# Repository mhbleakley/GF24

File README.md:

# GeoFence 2024

A dog collar with GNSS capabilities and an alarm, allowing the user to set a virtual fenced area. When the collar leaves the fenced area, the alarm sounds.

View schematic/board [here](https://kicanvas.org/?github=https%3A%2F%2Fgithub.com%2Fmhbleakley%2FGF24) (you will have to select board or schematic from right panel).

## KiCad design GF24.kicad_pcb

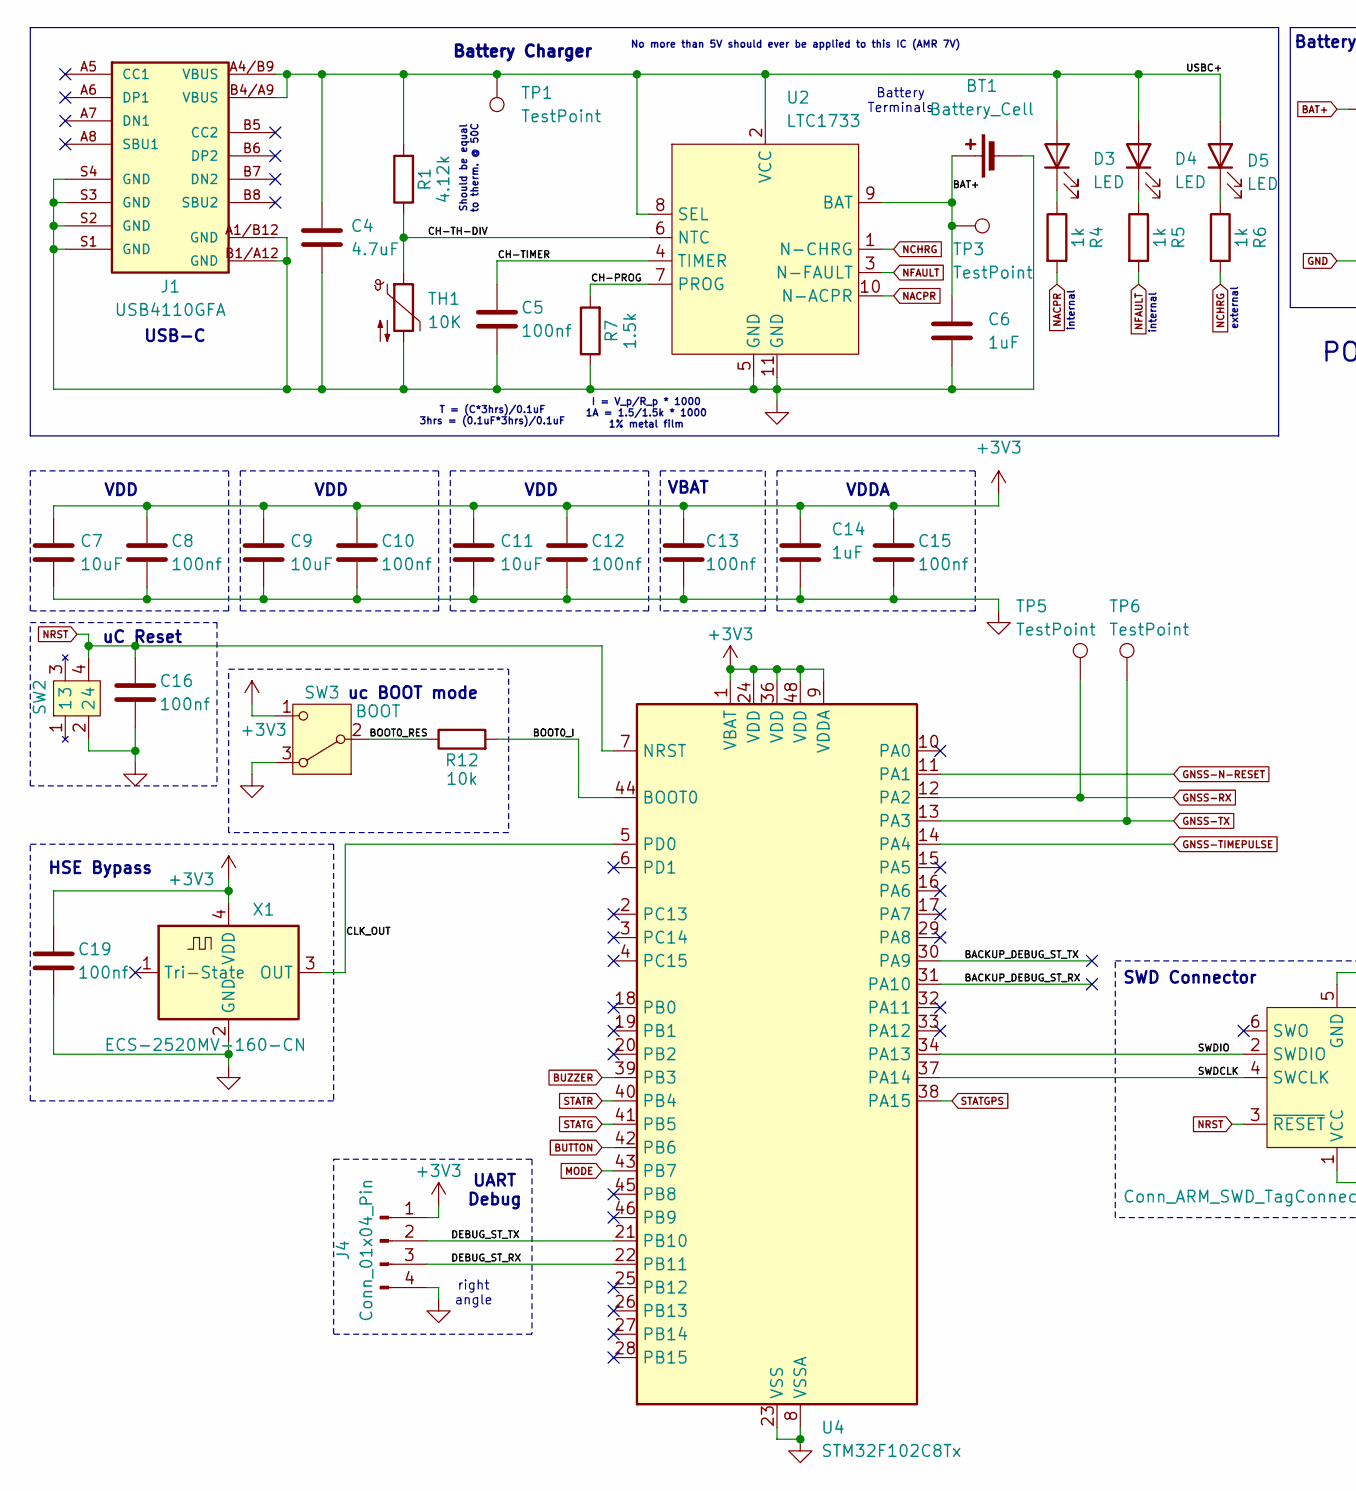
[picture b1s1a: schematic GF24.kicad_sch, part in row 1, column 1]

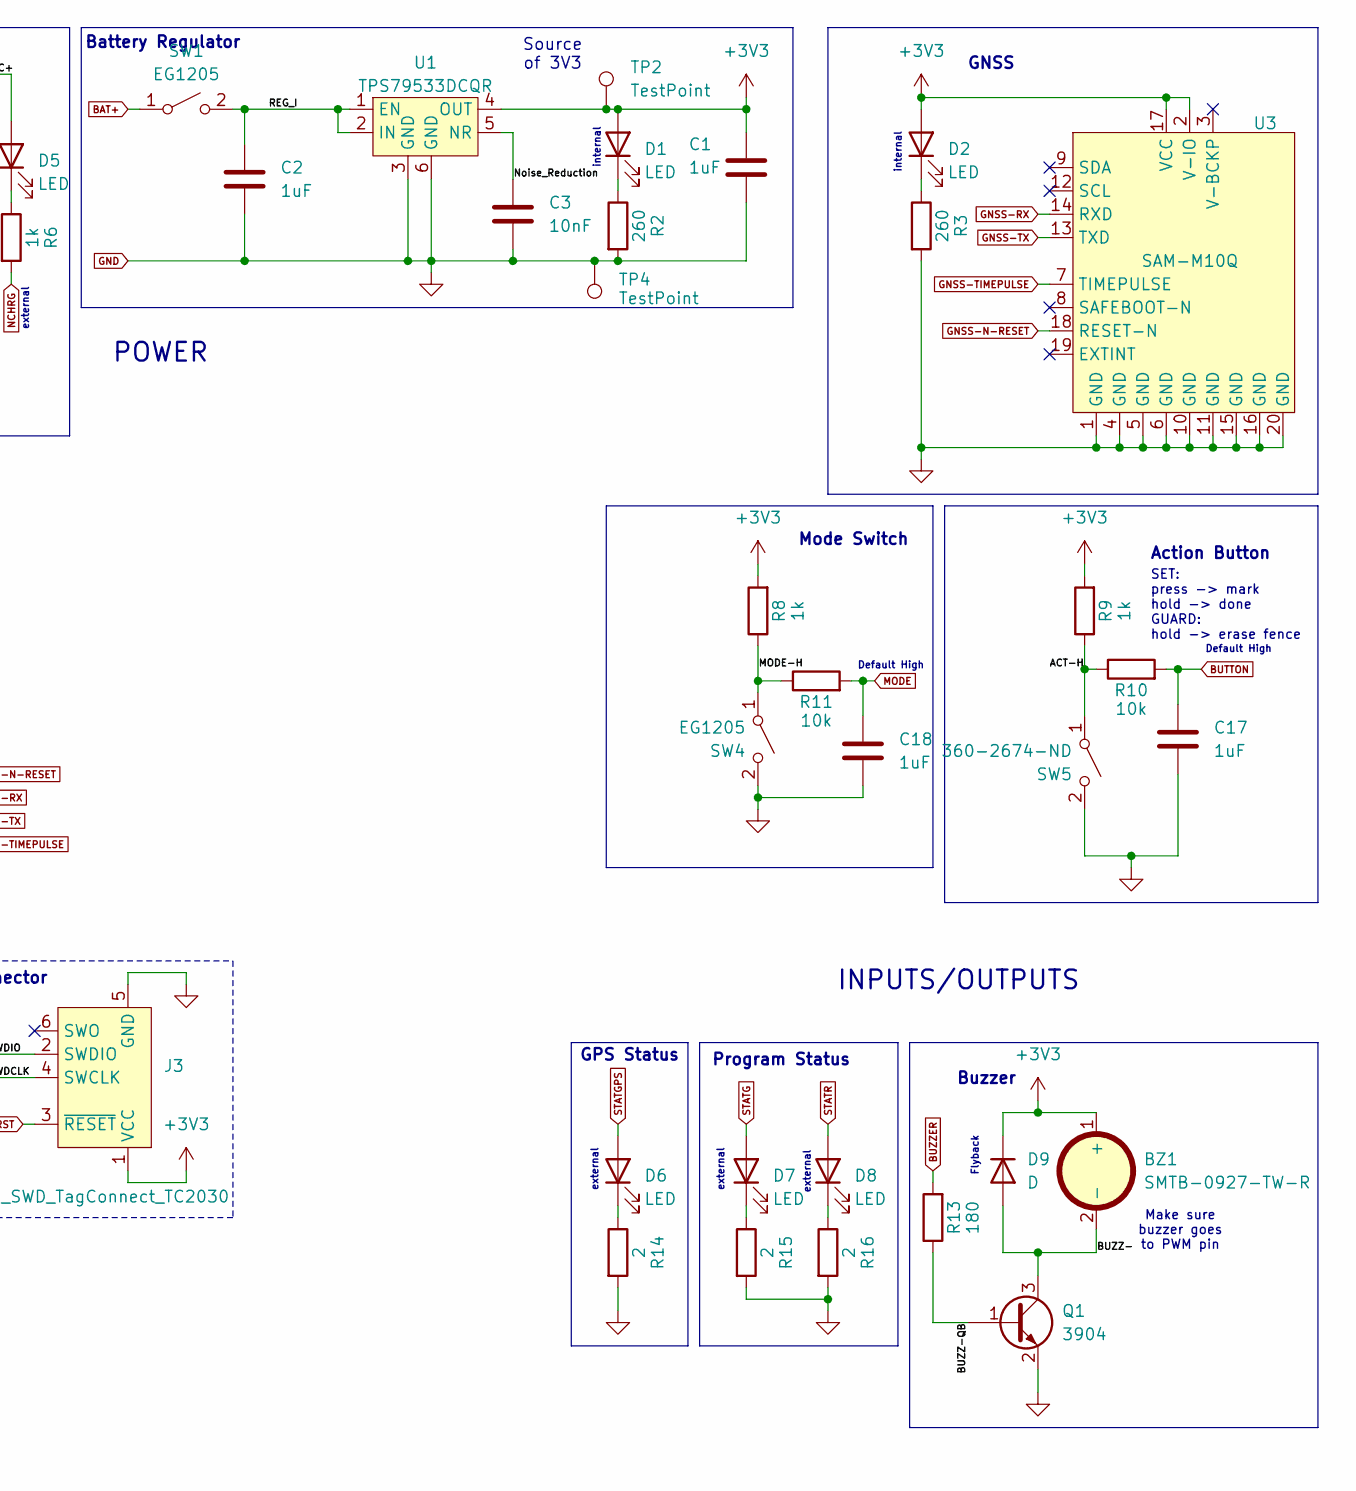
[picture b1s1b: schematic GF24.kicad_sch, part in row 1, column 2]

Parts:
BT1: Battery_Cell; Solder_Joint_1_2
BZ1: SMTB-0927-TW-R; Manufacturer PN 668-SMTB-0927-TW-RTR-ND
C1, C2, C6, C14, C17, C18: 1uF; C_0603_1608Metric; Manufacturer PN 399-13217-2-ND
C3: 10nF; C_0603_1608Metric; Manufacturer PN 399-C0603C103K8RACTUTR-ND
C4: 4.7uF; C_0805_2012Metric; Manufacturer PN 399-C1210C475K8RACTUTR-ND
C5, C8, C10, C12, C13, C15, C16, C19: 100nf; C_0805_2012Metric; Manufacturer PN 399-C0805C104K8RACTUTR-ND
C7, C9, C11: 10uF; C_0805_2012Metric; Manufacturer PN 399-C1210C106K8RACTUTR-ND
D1, D2, D3, D4: LED; WE-0603-Mono-Chip-Advance; Manufacturer PN 732-150060RS75003TR-ND
D5, D6, D7, D8: LED; WE-1204-Mono-Side; Manufacturer PN 732-5024-2-ND
D9: D; SOD-123-2; Manufacturer PN MMSD4148T1GOSTR-ND
J1: USB4110GFA; GCT_USB4110GFA; Manufacturer PN 2073-USB4110-GF-A-2-ND; DigiKey_Part_Number 2073-USB4110-GF-A-2-ND
J3: Conn_ARM_SWD_TagConnect_TC2030; Tag-Connect_TC2030-IDC-FP_2x03_P1.27mm_Vertical
J4: Conn_01x04_Pin; PinHeader_1x04_P2.54mm_Horizontal; Manufacturer PN S9016E-04-ND
Q1: 3904; SOT-323_SC-70; Manufacturer PN MMBT3904LT1GOSTR-ND
R1: 4.12k; R0603_medium; Manufacturer PN 311-4.12KHRTR-ND
R2, R3: 260; R0603_medium; Manufacturer PN 311-261HRTR-ND
R4, R5, R6, R8, R9: 1k; R0603_medium; Manufacturer PN 311-1.00KHRTR-ND
R7: 1.5k; R0603_medium; Manufacturer PN 311-1.50KHRTR-ND
R10, R11, R12: 10k; R0603_medium; Manufacturer PN 311-10.0KHRTR-ND
R13: 180; R0603_medium; Manufacturer PN 311-180HRTR-ND
R14, R15, R16: 2; R0603_medium; Manufacturer PN 13-RC0603JR-072RLTR-ND
SW1, SW4: EG1205; Solder_Joint_1_2
SW2: PTS815SJM250SMTRLFS; Manufacturer PN CKN12215-2-ND
SW3: BOOT; Nidec_Copal_CAS-120A; Manufacturer PN 563-1021-2-ND
SW5: 360-2674-ND; Solder_Joint_1_2
TH1: 10K; R0603_medium; Manufacturer PN 490-18139-2-ND
TP1, TP2, TP3, TP4, TP5, TP6: TestPoint; TestPoint_Pad_D1.5mm
U1: TPS79533DCQR; SOT-223-6; Manufacturer PN 296-13810-2-ND
U2: LTC1733; 10-MSOP-TE; Manufacturer PN LTC1733EMSE#TRPBFTR-ND
U3: SAM-M10Q; Manufacturer PN 672-SAM-M10Q-00BTR-ND
U4: STM32F102C8Tx; LQFP-48_7x7mm_P0.5mm; Manufacturer PN 497-8307-ND
X1: ECS-2520MV-160-CN; Oscillator_SMD_ECS_2520MV-xxx-xx-4Pin_2.5x2.0mm; Manufacturer PN XC3030TR-ND

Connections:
+3V3: BZ1.1 (+), C1.1, C7.1, C8.1, C9.1, C10.1, C11.1, C12.1, C13.1, C14.1, C15.1, C19.1, D1.2 (A), D2.2 (A), D9.1 (K), J3.1 (VCC), J4.1, R8.2, R9.2, SW3.1 (C), TP2.1, U1.4 (OUT), U3.2 (V-IO), U3.17 (VCC), U4.1 (VBAT), U4.9 (VDDA), U4.24 (VDD), U4.36 (VDD), U4.48 (VDD), X1.4 (VDD)
/ACT-H: R9.1, R10.1, SW5.1 (A)
/BACKUP_DEBUG_ST_RX: U4.31 (PA10)
/BACKUP_DEBUG_ST_TX: U4.30 (PA9)
/BOOT0_I: R12.2, U4.44 (BOOT0)
/BOOT0_RES: R12.1, SW3.2 (B)
/BUZZ-: BZ1.2 (-), D9.2 (A), Q1.3 (C)
/BUZZ-QB: Q1.1 (B), R13.1
/CH-PROG: R7.2, U2.7 (PROG)
/CH-TH-DIV: R1.1, TH1.1, U2.6 (NTC)
/CH-TIMER: C5.1, U2.4 (TIMER)
/CLK_OUT: U4.5 (PD0), X1.3 (OUT)
/DEBUG_ST_RX: J4.3, U4.22 (PB11)
/DEBUG_ST_TX: J4.2, U4.21 (PB10)
/MODE-H: R8.1, R11.1, SW4.1 (A)
/Noise_Reduction: C3.1, U1.5 (NR)
/REG_I: C2.1, SW1.2 (B), U1.1 (EN), U1.2 (IN)
/SWDCLK: J3.4 (SWCLK), U4.37 (PA14)
/SWDIO: J3.2 (SWDIO), U4.34 (PA13)
/USBC+: C4.1, D3.2 (A), D4.2 (A), D5.2 (A), J1.A4/B9 (VBUS), J1.B4/A9 (VBUS), R1.2, TP1.1, U2.2 (VCC), U2.8 (SEL)
BAT+: BT1.1 (+), C6.1, SW1.1 (A), TP3.1, U2.9 (BAT)
BUTTON: C17.1, R10.2, U4.42 (PB6)
BUZZER: R13.2, U4.39 (PB3)
GND: BT1.2 (-), C1.2, C2.2, C3.2, C4.2, C5.2, C6.2, C7.2, C8.2, C9.2, C10.2, C11.2, C12.2, C13.2, C14.2, C15.2, C16.2, C17.2, C18.2, C19.2, J1.A1/B12 (GND), J1.B1/A12 (GND), J1.S1 (GND), J1.S2 (GND), J1.S3 (GND), J1.S4 (GND), J3.5 (GND), J4.4, Q1.2 (E), R2.2, R3.2, R7.1, R14.2, R15.2, R16.2, SW2.2, SW3.3 (A), SW4.2 (B), SW5.2 (B), TH1.2, TP4.1, U1.3 (GND), U1.6 (GND), U2.5 (GND), U2.11 (GND), U3.1 (GND), U3.4 (GND), U3.5 (GND), U3.6 (GND), U3.10 (GND), U3.11 (GND), U3.15 (GND), U3.16 (GND), U3.20 (GND), U4.8 (VSSA), U4.23 (VSS), U4.35 (VSS), U4.47 (VSS), X1.2 (GND)
GNSS-N-RESET: U3.18 (RESET-N), U4.11 (PA1)
GNSS-RX: TP5.1, U3.14 (RXD), U4.12 (PA2)
GNSS-TIMEPULSE: U3.7 (TIMEPULSE), U4.14 (PA4)
GNSS-TX: TP6.1, U3.13 (TXD), U4.13 (PA3)
MODE: C18.1, R11.2, U4.43 (PB7)
NACPR: R4.2, U2.10 (N-ACPR)
NCHRG: R6.2, U2.1 (N-CHRG)
NFAULT: R5.2, U2.3 (N-FAULT)
NRST: C16.1, J3.3 (~RESET), SW2.4, U4.7 (NRST)
unnamed: D1.1 (K), R2.1
unnamed: D2.1 (K), R3.1
unnamed: D3.1 (K), R4.1
unnamed: D4.1 (K), R5.1
unnamed: D5.1 (K), R6.1
unnamed: D6.1 (K), R14.1
unnamed: D7.1 (K), R15.1
unnamed: D8.1 (K), R16.1
STATG: D7.2 (A), U4.41 (PB5)
STATGPS: D6.2 (A), U4.38 (PA15)
STATR: D8.2 (A), U4.40 (PB4)

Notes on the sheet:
Default High
SET: press -> mark hold -> done GUARD: hold -> erase fence
VDD
Should be equal to therm. @ 50C
external
Battery Terminals
INPUTS/OUTPUTS
internal
VDDA
USB-C
Buzzer
POWER
GNSS
right angle
uc BOOT mode
Mode Switch
Flyback
T = (C*3hrs)/0.1uF 3hrs = (0.1uF*3hrs)/0.1uF
UART Debug
uC Reset
Program Status
SWD Connector
GPS Status
No more than 5V should ever be applied to this IC (AMR 7V)
Source of 3V3
VBAT
Make sure buzzer goes to PWM pin
Battery Regulator
HSE Bypass
I = V_p/R_p * 1000 1A = 1.5/1.5k * 1000 1% metal film
Battery Charger
Action Button

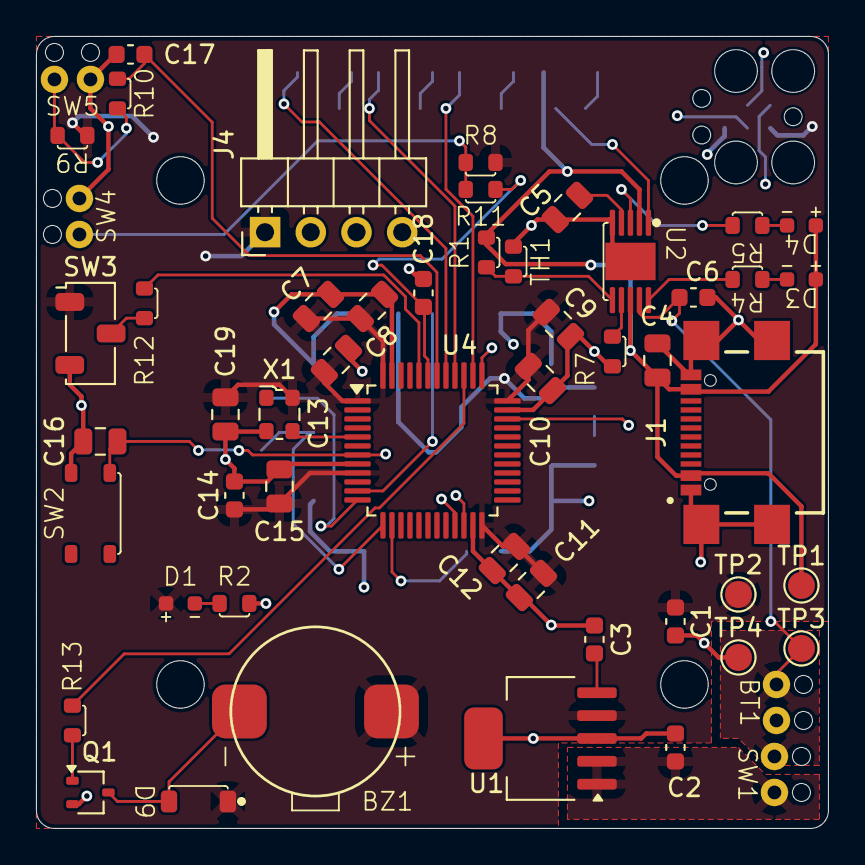
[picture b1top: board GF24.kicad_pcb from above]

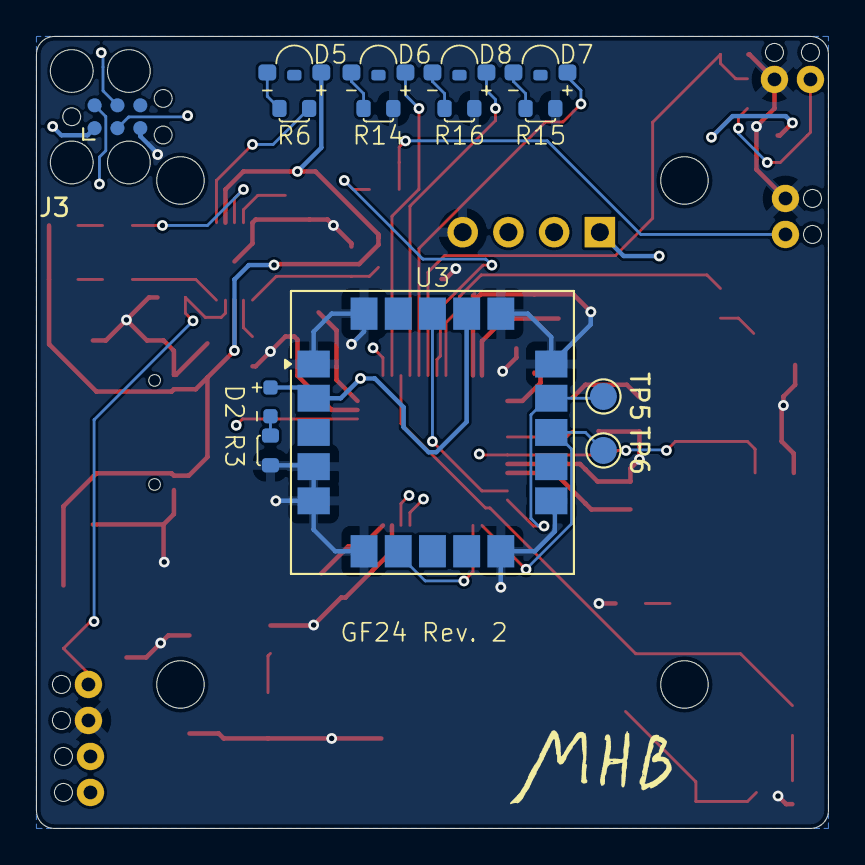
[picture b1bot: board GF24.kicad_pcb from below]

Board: 4 copper layers, 44.0 x 44.0 mm, 67 parts (14 on the bottom side), 42 nets.

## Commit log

2024-12-15 updated power
2024-12-15 forgot about the .lck
2024-12-15 switching devices
2024-12-16 changed NRST
2024-12-17 sorted BOOT0 for now, added HSE
2024-12-20 added MAX-M10S symbol/footprint
2024-12-22 didn't update
2024-12-24 added cap footprints
2024-12-26 added boot mode and battery
2024-12-26 added voltage regulator
2024-12-27 added all footprints, not all final
2024-12-28 buzzer
2024-12-29 someday I'll write useful commit messages
2024-12-30 button circuit complete
2024-12-31 added initial battery charge circuit
2024-12-31 added passives
2024-12-31 idk lol
2025-01-02 beats me
2025-01-03 selected components for battery charger
2025-01-06 updated battery regulator circuit. oof
2025-01-07 started to add EEPROM
2025-01-10 swapped GNSS again. Close to done with schematic
2025-01-10 added status LEDs
2025-01-10 updated again lol
2025-01-11 fixed PG indicator, grouped parts functionally
2025-01-11 changed most LED circuits which deal with open drain outputs
2025-01-12 fixed other LEDs, added or edited many footprints
2025-01-12 forgot these deletions
2025-01-12 schematic done. most footprints done. now for the layout. oof
2025-01-12 nothing
2025-01-21 some layout changes
2025-01-22 'test'
2025-01-23 started traces. need to check footprints are correct i.e. regulator
2025-01-23 drew 3v plane
2025-01-24 removed broken symbol
2025-01-24 fixed broken footprint
2025-01-24 fixed some small ERC/DRC issues
2025-01-24 updated power planes
2025-01-25 possibly done with routing
2025-01-25 gerber and drill test
2025-01-27 not sure if there are any changes here
2025-02-06 going to try and reroute everything
2025-02-09 making things smaller
2025-02-10 added mouse bites. need to do stackup
2025-02-10 board setup mostly complete. need to do net classes properly
2025-02-10 initial layout
2025-02-11 another round of layout
2025-02-11 still need to add test points, BOM
2025-02-13 added some final touches
2025-02-15 no actual changes
2025-03-10 added pos files
2025-04-10 Rev 1
2025-04-12 swapped buzzer
2025-04-14 changed LEDs for charging
2025-04-14 started wiring 555
2025-04-19 test
2025-05-06 updating regulator
2025-05-09 soft complete Rev 2 schematic
2025-05-16 changed status LEDs based on testing
2025-05-18 need to finish placement but this is an almost completed R2
2025-05-22 going to make some changes to the I/O
2025-05-22 added Wago
2025-05-27 3D done, started routing
2025-05-28 finished routing for Rev 2
2025-05-29 updated BOM, ordered board/components
2025-06-21 I ordered the wrong size capacitors
